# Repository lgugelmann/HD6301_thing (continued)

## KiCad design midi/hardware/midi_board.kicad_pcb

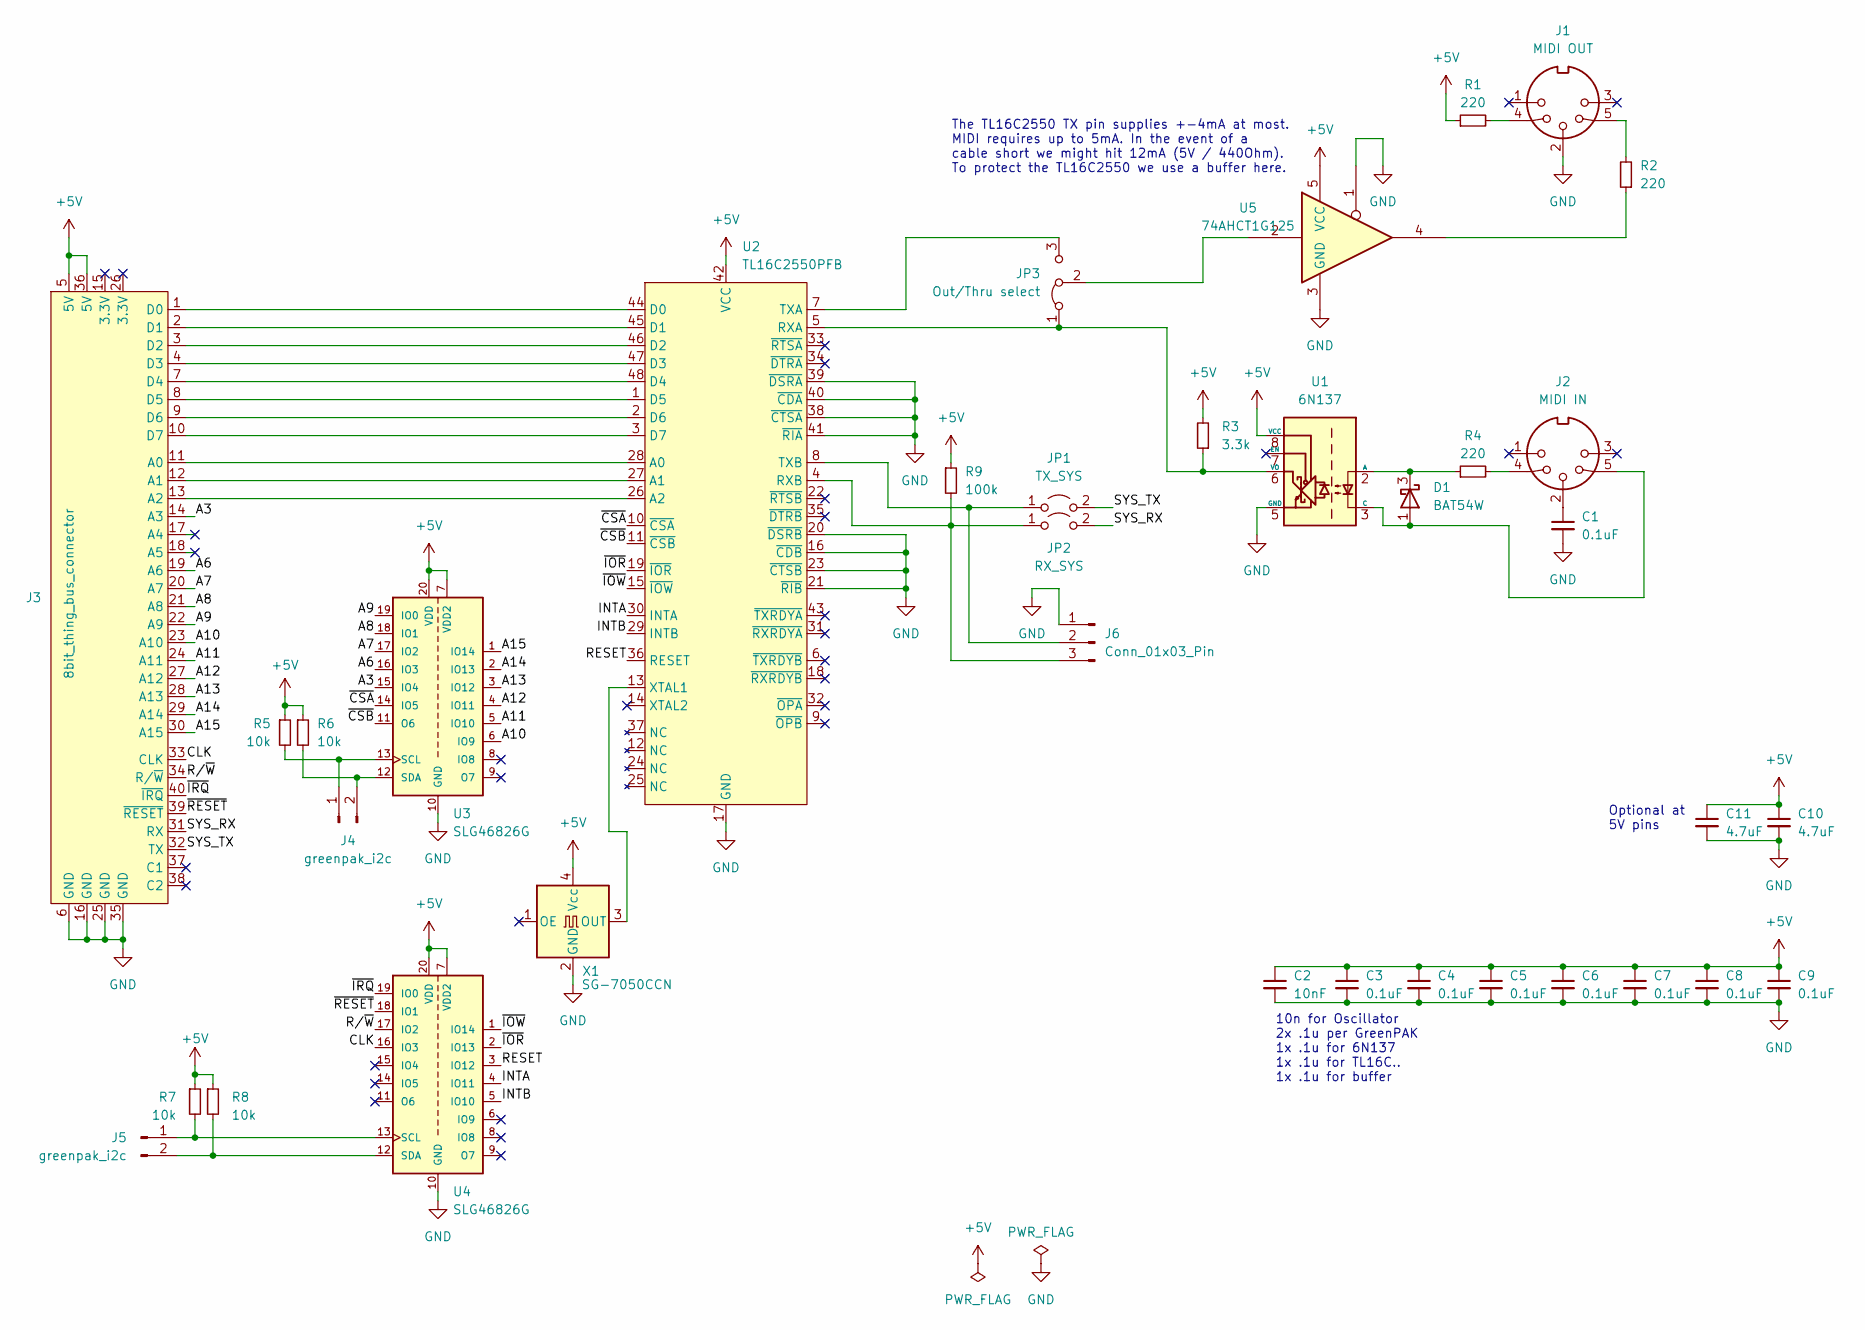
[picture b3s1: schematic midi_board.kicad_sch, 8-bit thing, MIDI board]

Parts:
C1, C3, C4, C5, C6, C7, C8, C9: 0.1uF; C_0805_2012Metric_Pad1.18x1.45mm_HandSolder
C2: 10nF; C_0805_2012Metric_Pad1.18x1.45mm_HandSolder
C10, C11: 4.7uF; C_0805_2012Metric_Pad1.18x1.45mm_HandSolder
D1: BAT54W; SOT-323_SC-70_Handsoldering
J1: MIDI OUT; Kycon-KCDX-5S-N
J2: MIDI IN; Kycon-KCDX-5S-N
J3: 8bit_thing_bus_connector; IDC-Header_2x20_P2.54mm_Horizontal
J4, J5: greenpak_i2c; PinHeader_1x02_P2.54mm_Vertical_minimal
J6: Conn_01x03_Pin; PinHeader_1x03_P2.54mm_Horizontal
JP1: TX_SYS; PinHeader_1x02_P2.54mm_Vertical_minimal
JP2: RX_SYS; PinHeader_1x02_P2.54mm_Vertical_minimal
JP3: Out/Thru select; PinHeader_1x03_P2.54mm_2_options_jumper_reverse
R1, R2: 220; R_0805_2012Metric_Pad1.20x1.40mm_HandSolder
R3: 3.3k; R_0805_2012Metric_Pad1.20x1.40mm_HandSolder
R4: 220; C_0805_2012Metric_Pad1.18x1.45mm_HandSolder
R5, R6, R7, R8: 10k; R_0805_2012Metric_Pad1.20x1.40mm_HandSolder
R9: 100k; R_0805_2012Metric_Pad1.20x1.40mm_HandSolder
U1: 6N137; DIP-8_W7.62mm
U2: TL16C2550PFB; TQFP-48_7x7mm_P0.5mm
U3, U4: SLG46826G; SOP65P640X120-20N; PARTREV 3.10
U5: 74AHCT1G125; SOT-353_SC-70-5_Handsoldering
X1: SG-7050CCN; Oscillator_SMD_SeikoEpson_SG8002CA-4Pin_7.0x5.0mm

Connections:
+5V: C2.1, C3.1, C4.1, C5.1, C6.1, C7.1, C8.1, C9.1, C10.1, C11.1, J3.5 (5V), J3.36 (5V), R1.1, R3.2, R5.1, R6.1, R7.1, R8.1, R9.1, U1.8 (VCC), U2.42 (VCC), U3.7 (VDD2), U3.20 (VDD), U4.7 (VDD2), U4.20 (VDD), U5.5 (VCC), X1.4 (Vcc)
/A3: J3.14 (A3), U3.15 (IO4)
/A6: J3.19 (A6), U3.16 (IO3)
/A7: J3.20 (A7), U3.17 (IO2)
/A8: J3.21 (A8), U3.18 (IO1)
/A9: J3.22 (A9), U3.19 (IO0)
/A10: J3.23 (A10), U3.6 (IO9)
/A11: J3.24 (A11), U3.5 (IO10)
/A12: J3.27 (A12), U3.4 (IO11)
/A13: J3.28 (A13), U3.3 (IO12)
/A14: J3.29 (A14), U3.2 (IO13)
/A15: J3.30 (A15), U3.1 (IO14)
/CLK: J3.33 (CLK), U4.16 (IO3)
/INTA: U2.30 (INTA), U4.4 (IO11)
/INTB: U2.29 (INTB), U4.5 (IO10)
/RESET: U2.36 (RESET), U4.3 (IO12)
/R/~W: J3.34 (R/~W), U4.17 (IO2)
/SYS_RX: J3.31 (RX), JP2.2 (B)
/SYS_TX: J3.32 (TX), JP1.2 (B)
/~CSA: U2.10 (~CSA), U3.14 (IO5)
/~CSB: U2.11 (~CSB), U3.11 (O6)
/~IOR: U2.19 (~IOR), U4.2 (IO13)
/~IOW: U2.15 (~IOW), U4.1 (IO14)
/~IRQ: J3.40 (~IRQ), U4.19 (IO0)
/~RESET: J3.39 (~RESET), U4.18 (IO1)
GND: C1.2, C2.2, C3.2, C4.2, C5.2, C6.2, C7.2, C8.2, C9.2, C10.2, C11.2, J1.2, J3.6 (GND), J3.16 (GND), J3.25 (GND), J3.35 (GND), J6.1, U1.5 (GND), U2.16 (~CDB), U2.17 (GND), U2.20 (~DSRB), U2.21 (~RIB), U2.23 (~CTSB), U2.38 (~CTSA), U2.39 (~DSRA), U2.40 (~CDA), U2.41 (~RIA), U3.10 (GND), U4.10 (GND), U5.1, U5.3 (GND), X1.2 (GND)
unnamed: C1.1, J2.2
unnamed: D1.1 (A), J2.5, U1.3 (C)
unnamed: D1.3 (K), R4.1, U1.2 (A)
unnamed: J1.4, R1.2
unnamed: J1.5, R2.2
unnamed: J2.4, R4.2
unnamed: J3.11 (A0), U2.28 (A0)
unnamed: J3.12 (A1), U2.27 (A1)
unnamed: J3.13 (A2), U2.26 (A2)
unnamed: J3.1 (D0), U2.44 (D0)
unnamed: J3.2 (D1), U2.45 (D1)
unnamed: J3.3 (D2), U2.46 (D2)
unnamed: J3.4 (D3), U2.47 (D3)
unnamed: J3.7 (D4), U2.48 (D4)
unnamed: J3.8 (D5), U2.1 (D5)
unnamed: J3.9 (D6), U2.2 (D6)
unnamed: J3.10 (D7), U2.3 (D7)
unnamed: J4.1, R5.2, U3.13 (SCL)
unnamed: J4.2, R6.2, U3.12 (SDA)
unnamed: J5.1, R7.2, U4.13 (SCL)
unnamed: J5.2, R8.2, U4.12 (SDA)
unnamed: J6.2, JP1.1 (A), U2.8 (TXB)
unnamed: J6.3, JP2.1 (A), R9.2, U2.4 (RXB)
unnamed: JP3.1 (A), R3.1, U1.6 (VO), U2.5 (RXA)
unnamed: JP3.3 (B), U2.7 (TXA)
unnamed: JP3.2 (C), U5.2
unnamed: R2.1, U5.4
unnamed: U2.13 (XTAL1), X1.3 (OUT)

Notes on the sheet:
The TL16C2550 TX pin supplies +-4mA at most. MIDI requires up to 5mA. In the event of a cable short we might hit 12mA (5V / 440Ohm). To protect the TL16C2550 we use a buffer here.
10n for Oscillator 2x .1u per GreenPAK 1x .1u for 6N137 1x .1u for TL16C.. 1x .1u for buffer
Optional at 5V pins

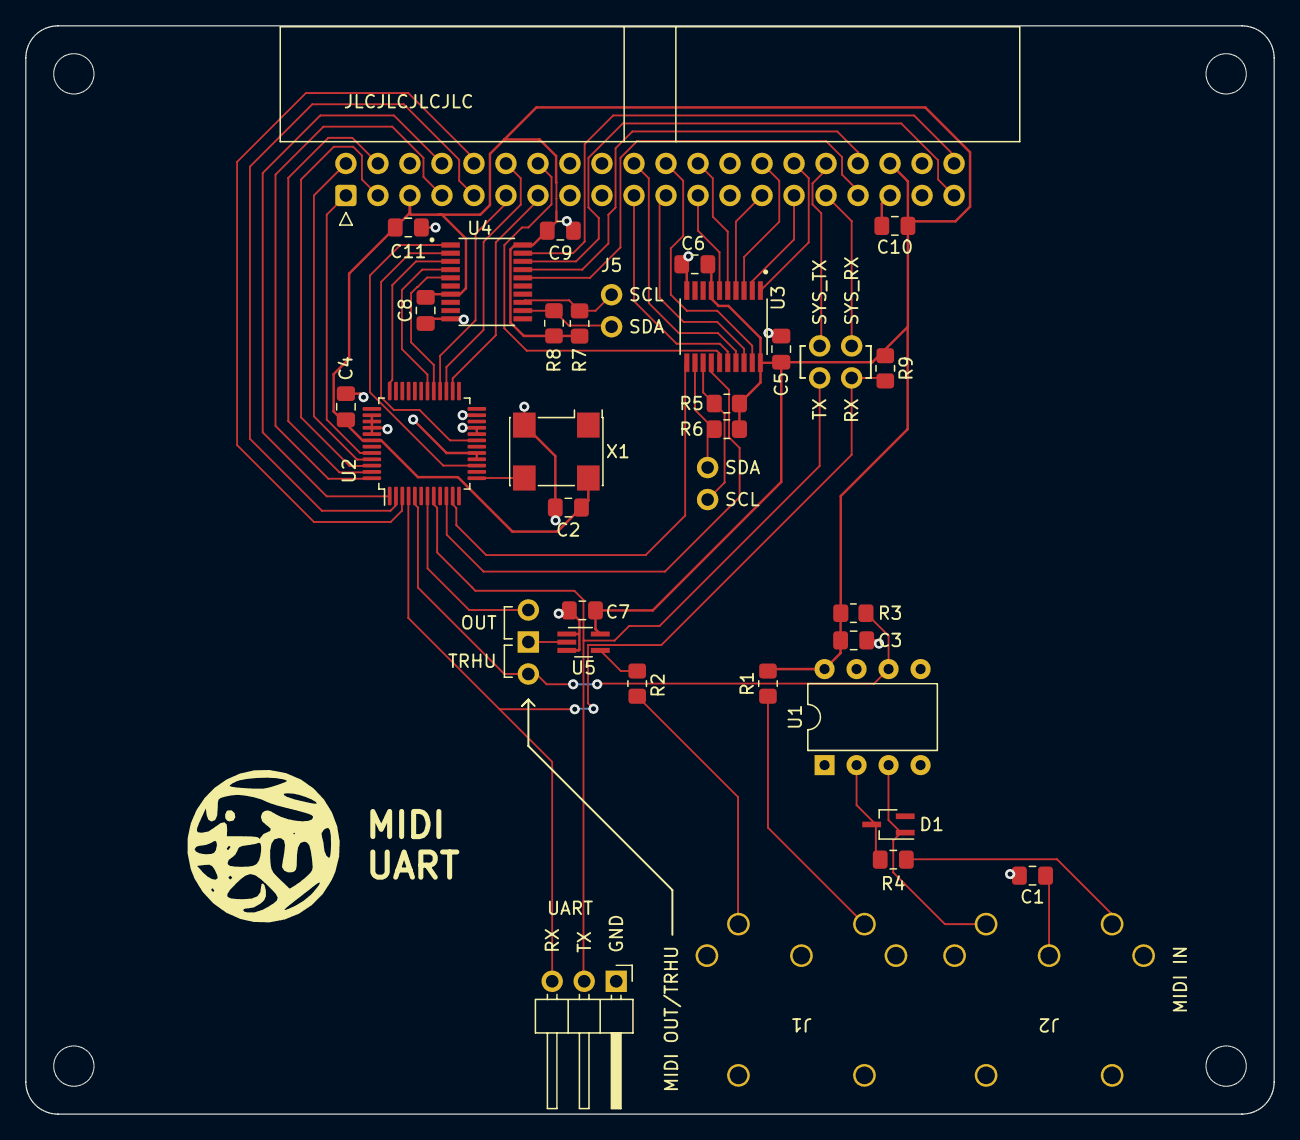
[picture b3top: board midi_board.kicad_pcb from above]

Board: 2 copper layers, 99.1 x 86.4 mm, 36 parts (0 on the bottom side), 54 nets.

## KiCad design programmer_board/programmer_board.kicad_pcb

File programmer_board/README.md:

# Pi Pico programmer board

> ***WARNING***
> the 1.0 version of the board is buggy. At a minimum it requires adding
> pullups on all OE pins. The Pico does not start quickly enough to put them into
> a good state. The resulting bus contention uses enough power to render the Pico
> unable to start. For any sane current limit the '5V' rail gets drawn down to
> less than the ~1.8V needed for the Pico boost converter to start working. The
> Schematic & PCB have not been updated to fix this bug yet. It's not hard to fix
> the v1.0 board by reworking some extra resistors onto it.

A common way to program ROMs for 8-bit hobby projects are ZIF sockets. Take ROM
out, put it into programmer, program it, put it back into the ZIF socket,
run. That works, but it gets tedious _really fast_. It's also getting harder and
harder to find parallel ROMs in DIP packages at reasonable prices. The solution
is to bite the bullet and use soldered-down ROMs in smaller packages and figure
out in-circuit programming.

The goal here is to make programming the HD6301 board as easy as programming an
Arduino from a modern computer, while at the same time keeping the HD6301 board
able to work independently without this development companion.

This is accomplished by having a Pi Pico expose a serial console to receive
commands from a computer. To program the HD6301 board the Pico puts the CPU into
standby mode, takes over the bus, reads or writes to arbitrary memory locations
(which allows it to program the ROM among other things), and wakes the HD6301
back up.

This technique makes for a fairly generic interface to many 8-bit era
devices. It could work easily for a 6502-based computer as well (at least for
versions with a bus-enable line).

Programming 8k (2 sectors) of ROM takes just a few seconds.

The board itself is pretty simple. The main issue is that the Pico does not have
enough I/O lines, and that it's not 5V tolerant. This means we need both
multiplexing and voltage translation. The address and data pins are all
connected in groups of 8 pins to a pair of 74LVC245 bus buffers and 74HCT573
latches. The latch holds the output data, while the '245 does voltage
translation for inputs. It's up to the software on the Pico to correctly juggle
the various output enable pins to avoid bus contention. The remaining lines are
voltage-translated by a GreenPAK programmable logic chip that can do 3.3V on
some GPIOs and 5V, tri-state on others.

The Pico was chosen here because it's trivial to prototype with it and it makes
it easy to expose 2 serial lines on the USB side. One is used for programming,
and one to communicate with the HD6301's own serial interface.

The initial plan was to use a much dumber chip like FTDI USB interfaces and put
all the logic on the other side of the serial interface. USB latency(!) made
that plan unworkable. See below for the details.

## TODOs for the next revision

- Add pull-ups on all OE pins and D0..D7 to guarantee safe initial state
- Jumpers for all power rails to isolate the Pico
- Some solution for power rail filtering. My desktop's USB ports are
  _NOISY_. Not a problem for digital work - but the OPL3 audio board suffers
  from bad filtering here.

## In-circuit programming via USB - the gory details

## FT231x solution

At first I explored using an FTDI FT231x. It's 5V compatible and conveniently
also gets us USB serial. It has an 8-pin bitbang mode and 4 additional 'CBUS'
lines. Those can be programmed to be GPIOs, write strobes, and more.

The first solution was to use the 8bit GPIOs for data and CBUS for control
lines. Unfortunately the CBUS GPIO mode can't be used concurrently with the
bitbang mode and switching between bitbang and CBUS takes a _long_ time (think
hundreds of ms). Switching between the two for every byte makes things
unworkably slow.

Next up I turned to putting glue logic on a GreenPAK chip and using the
write-strobe mode. This works really nicely: first write puts the chip in
standby, subsequent writes latch data, address low, address high onto '74xx573
latches, and after that the GreenPAK automatically strobes clock & R/W. After a
few hundred ms without activity everything resets and the 6301 wakes back up.

This works really nicely for a write-only in-circuit programmer. There is a
tested working python-based programmer and the necessary GreenPAK glue logic in
this repo. I didn't push for performance but got to ~15 seconds to write a 32K
ROM.

Next up I tried to figure out how to implement a read-mode as well. In theory it
should be easy: put a 74'245 on the data bus, do the same latching trick as
before, but instead at the end bring OE low on the '245 and read the FT231x I/O
pins. A CBUS line can be used to put the GreenPAK into a read-mode with
different strobes / timings, but because that needs to be done only once at the
start it should be fast enough.

I got this to work - but it's sloooow because of USB latency, se below for
why. Tl;dr: switching between reading / writing on the FT231x for every byte
takes >1ms each time. This means 1 minute to read the whole address space at a
minimum. The fastest I could manage is ~3ms per byte before I gave up.

There could be possible solutions that do not require switching between reading
and writing at each byte. One option is to use a CBUS line for a read strobe and
discrete logic to increment an address counter at each strobe. You could set up
the counter at the start, then put the chip into read mode, and stream the data
back. This starts to get a bit silly and would also require futzing around with
the FT231x read buffers which seem to be particularly tricky to synchronize to
anything.

Another option is to use a synchronous bit-bang mode where a read is done on
every write and streamed back. The catch here is that you have to decide ahead
of time which pins are inputs and which are outputs. I could split the 8 bits
into 4 in / 4 out but that would also require extra glue logic that I didn't
feel like building.

### USB latency ruins the party

USB communication (before 3.0) is _always_ host-initiated. No usb device can
just decide to send data. It needs to be asked by the host whether there is
anything that it might want to send first. The fastest polling rate available
from the host side is 1ms.

This means that if switching between reading and writing requires a control
packet there is a mandatory 1ms latency hit: 1 packet with the writes (which can
be all sent bunched up into one), then a second packet with the command to
switch from read to write, then another packet to poll for the read data. On the
ft231x that's 2ms latency / byte at a minimum as we need to wait out the polling
interval twice.

### Pi Pico programmer

To avoid USB latency I need something capable of receiving a "read x bytes
starting at address y" command and then stream the data back. I have a spare Pi
Pico laying around so I went with that. It has enough I/O, has support for
multiple UARTs (so one for programming, one for comms with the HD6301), and
comes with both 5V and 3.3V rail which can be convenient. Downside: not 5V
tolerant.

The 5V issue is easy to solve: for the data output from the Pico I use
TTL-compatible '74xxT573 latches, for the data input to the Pico 3.3V '74LVHC245
buffers which are 5V tolerant. For the control lines I make use of the dual
supply feature of the _really really cool_ SLG46826 GreenPAK to have 3.3V I/O on
the Pico side and tri-state 5V I/O on the HD6301 bus side.

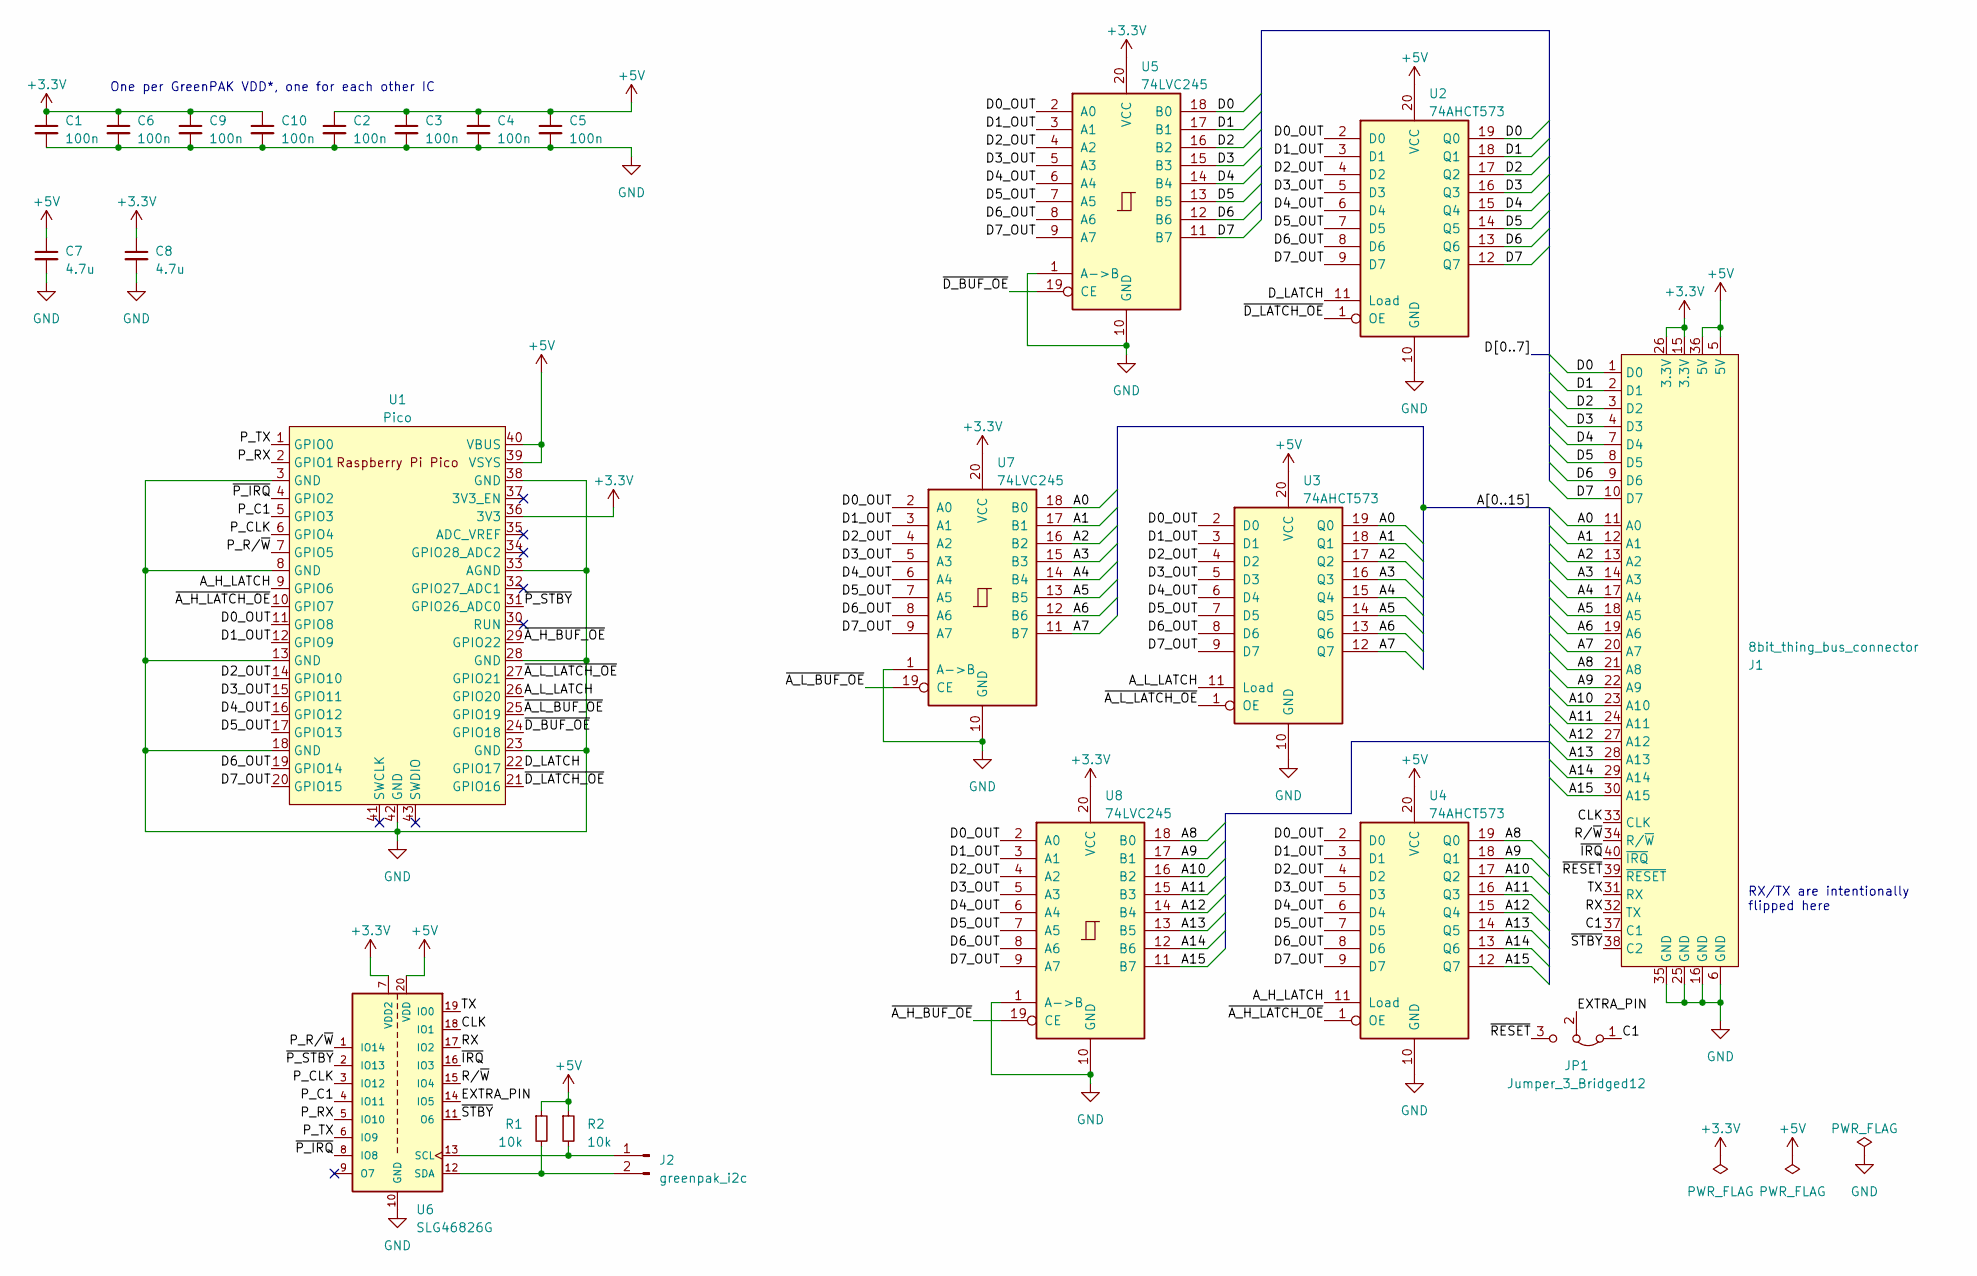
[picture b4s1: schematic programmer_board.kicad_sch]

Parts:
C1, C2, C3, C4, C5, C6, C9, C10: 100n; C_0805_2012Metric_Pad1.18x1.45mm_HandSolder
C7, C8: 4.7u; C_0805_2012Metric_Pad1.18x1.45mm_HandSolder
J1: 8bit_thing_bus_connector; IDC-Header_2x20_P2.54mm_Horizontal
J2: greenpak_i2c; PinHeader_1x02_P2.54mm_Vertical_minimal
JP1: Jumper_3_Bridged12; PinHeader_1x03_P2.54mm_Vertical
R1, R2: 10k; R_0805_2012Metric_Pad1.20x1.40mm_HandSolder
U1: Pico; RPi_Pico_SMD_TH
U2, U3, U4: 74AHCT573; SSOP-20_5.3x7.2mm_P0.65mm
U5, U7, U8: 74LVC245; TSSOP-20_4.4x6.5mm_P0.65mm
U6: SLG46826G; SOP65P640X120-20N; PARTREV 3.10

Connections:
+3.3V: C1.1, C6.1, C8.1, C9.1, C10.1, J1.15 (3.3V), J1.26 (3.3V), U1.36 (3V3), U5.20 (VCC), U6.7 (VDD2), U7.20 (VCC), U8.20 (VCC)
+5V: C2.1, C3.1, C4.1, C5.1, C7.1, J1.5 (5V), J1.36 (5V), R1.1, R2.1, U1.39 (VSYS), U1.40 (VBUS), U2.20 (VCC), U3.20 (VCC), U4.20 (VCC), U6.20 (VDD)
/A0: J1.11 (A0), U3.19 (Q0), U7.18 (B0)
/A1: J1.12 (A1), U3.18 (Q1), U7.17 (B1)
/A2: J1.13 (A2), U3.17 (Q2), U7.16 (B2)
/A3: J1.14 (A3), U3.16 (Q3), U7.15 (B3)
/A4: J1.17 (A4), U3.15 (Q4), U7.14 (B4)
/A5: J1.18 (A5), U3.14 (Q5), U7.13 (B5)
/A6: J1.19 (A6), U3.13 (Q6), U7.12 (B6)
/A7: J1.20 (A7), U3.12 (Q7), U7.11 (B7)
/A8: J1.21 (A8), U4.19 (Q0), U8.18 (B0)
/A9: J1.22 (A9), U4.18 (Q1), U8.17 (B1)
/A10: J1.23 (A10), U4.17 (Q2), U8.16 (B2)
/A11: J1.24 (A11), U4.16 (Q3), U8.15 (B3)
/A12: J1.27 (A12), U4.15 (Q4), U8.14 (B4)
/A13: J1.28 (A13), U4.14 (Q5), U8.13 (B5)
/A14: J1.29 (A14), U4.13 (Q6), U8.12 (B6)
/A15: J1.30 (A15), U4.12 (Q7), U8.11 (B7)
/A_H_LATCH: U1.9 (GPIO6), U4.11 (Load)
/A_L_LATCH: U1.26 (GPIO20), U3.11 (Load)
/C1: J1.37 (C1), JP1.1 (A)
/CLK: J1.33 (CLK), U6.18 (IO1)
/D0: J1.1 (D0), U2.19 (Q0), U5.18 (B0)
/D0_OUT: U1.11 (GPIO8), U2.2 (D0), U3.2 (D0), U4.2 (D0), U5.2 (A0), U7.2 (A0), U8.2 (A0)
/D1: J1.2 (D1), U2.18 (Q1), U5.17 (B1)
/D1_OUT: U1.12 (GPIO9), U2.3 (D1), U3.3 (D1), U4.3 (D1), U5.3 (A1), U7.3 (A1), U8.3 (A1)
/D2: J1.3 (D2), U2.17 (Q2), U5.16 (B2)
/D2_OUT: U1.14 (GPIO10), U2.4 (D2), U3.4 (D2), U4.4 (D2), U5.4 (A2), U7.4 (A2), U8.4 (A2)
/D3: J1.4 (D3), U2.16 (Q3), U5.15 (B3)
/D3_OUT: U1.15 (GPIO11), U2.5 (D3), U3.5 (D3), U4.5 (D3), U5.5 (A3), U7.5 (A3), U8.5 (A3)
/D4: J1.7 (D4), U2.15 (Q4), U5.14 (B4)
/D4_OUT: U1.16 (GPIO12), U2.6 (D4), U3.6 (D4), U4.6 (D4), U5.6 (A4), U7.6 (A4), U8.6 (A4)
/D5: J1.8 (D5), U2.14 (Q5), U5.13 (B5)
/D5_OUT: U1.17 (GPIO13), U2.7 (D5), U3.7 (D5), U4.7 (D5), U5.7 (A5), U7.7 (A5), U8.7 (A5)
/D6: J1.9 (D6), U2.13 (Q6), U5.12 (B6)
/D6_OUT: U1.19 (GPIO14), U2.8 (D6), U3.8 (D6), U4.8 (D6), U5.8 (A6), U7.8 (A6), U8.8 (A6)
/D7: J1.10 (D7), U2.12 (Q7), U5.11 (B7)
/D7_OUT: U1.20 (GPIO15), U2.9 (D7), U3.9 (D7), U4.9 (D7), U5.9 (A7), U7.9 (A7), U8.9 (A7)
/D_LATCH: U1.22 (GPIO17), U2.11 (Load)
/EXTRA_PIN: JP1.2 (C), U6.14 (IO5)
/P_C1: U1.5 (GPIO3), U6.4 (IO11)
/P_CLK: U1.6 (GPIO4), U6.3 (IO12)
/P_RX: U1.2 (GPIO1), U6.5 (IO10)
/P_R/~W: U1.7 (GPIO5), U6.1 (IO14)
/P_TX: U1.1 (GPIO0), U6.6 (IO9)
/RX: J1.32 (TX), U6.17 (IO2)
/R/~W: J1.34 (R/~W), U6.15 (IO4)
/TX: J1.31 (RX), U6.19 (IO0)
/~A_H_BUF_OE: U1.29 (GPIO22), U8.19 (CE)
/~A_H_LATCH_OE: U1.10 (GPIO7), U4.1 (OE)
/~A_L_BUF_OE: U1.25 (GPIO19), U7.19 (CE)
/~A_L_LATCH_OE: U1.27 (GPIO21), U3.1 (OE)
/~D_BUF_OE: U1.24 (GPIO18), U5.19 (CE)
/~D_LATCH_OE: U1.21 (GPIO16), U2.1 (OE)
/~IRQ: J1.40 (~IRQ), U6.16 (IO3)
/~P_IRQ: U1.4 (GPIO2), U6.8 (IO8)
/~P_STBY: U1.31 (GPIO26_ADC0), U6.2 (IO13)
/~RESET: J1.39 (~RESET), JP1.3 (B)
/~STBY: J1.38 (C2), U6.11 (O6)
GND: C1.2, C2.2, C3.2, C4.2, C5.2, C6.2, C7.2, C8.2, C9.2, C10.2, J1.6 (GND), J1.16 (GND), J1.25 (GND), J1.35 (GND), U1.3 (GND), U1.8 (GND), U1.13 (GND), U1.18 (GND), U1.23 (GND), U1.28 (GND), U1.33 (AGND), U1.38 (GND), U1.42 (GND), U2.10 (GND), U3.10 (GND), U4.10 (GND), U5.1 (A->B), U5.10 (GND), U6.10 (GND), U7.1 (A->B), U7.10 (GND), U8.1 (A->B), U8.10 (GND)
unnamed: J2.1, R2.2, U6.13 (SCL)
unnamed: J2.2, R1.2, U6.12 (SDA)

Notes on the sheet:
RX/TX are intentionally flipped here
One per GreenPAK VDD*, one for each other IC

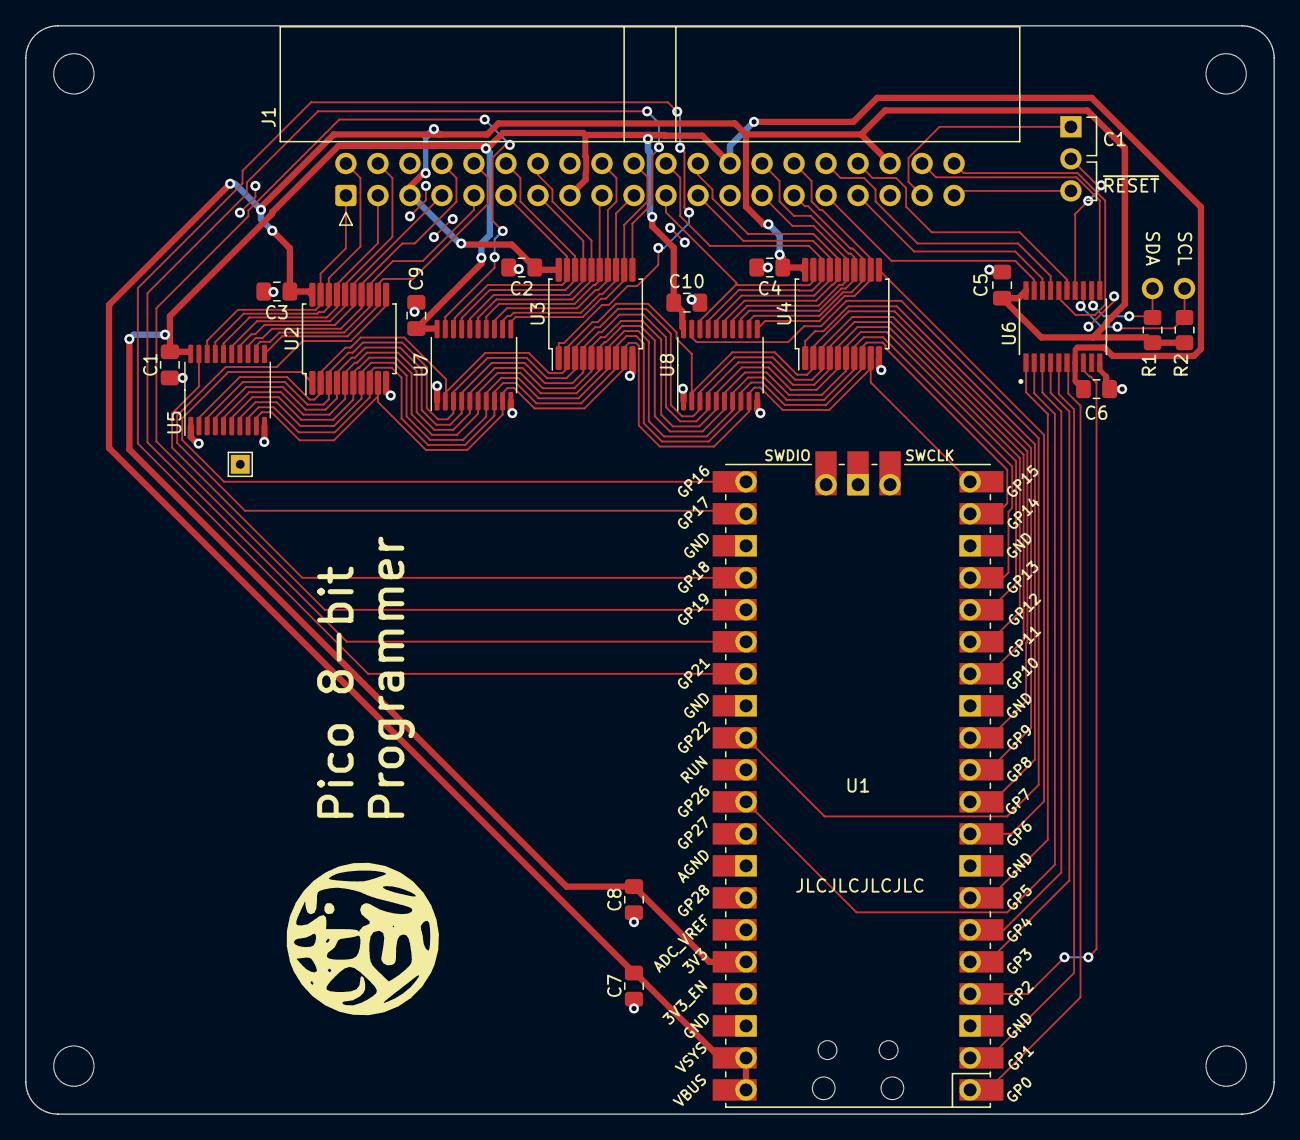
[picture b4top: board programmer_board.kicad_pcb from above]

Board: 2 copper layers, 99.1 x 86.4 mm, 23 parts (0 on the bottom side), 62 nets.

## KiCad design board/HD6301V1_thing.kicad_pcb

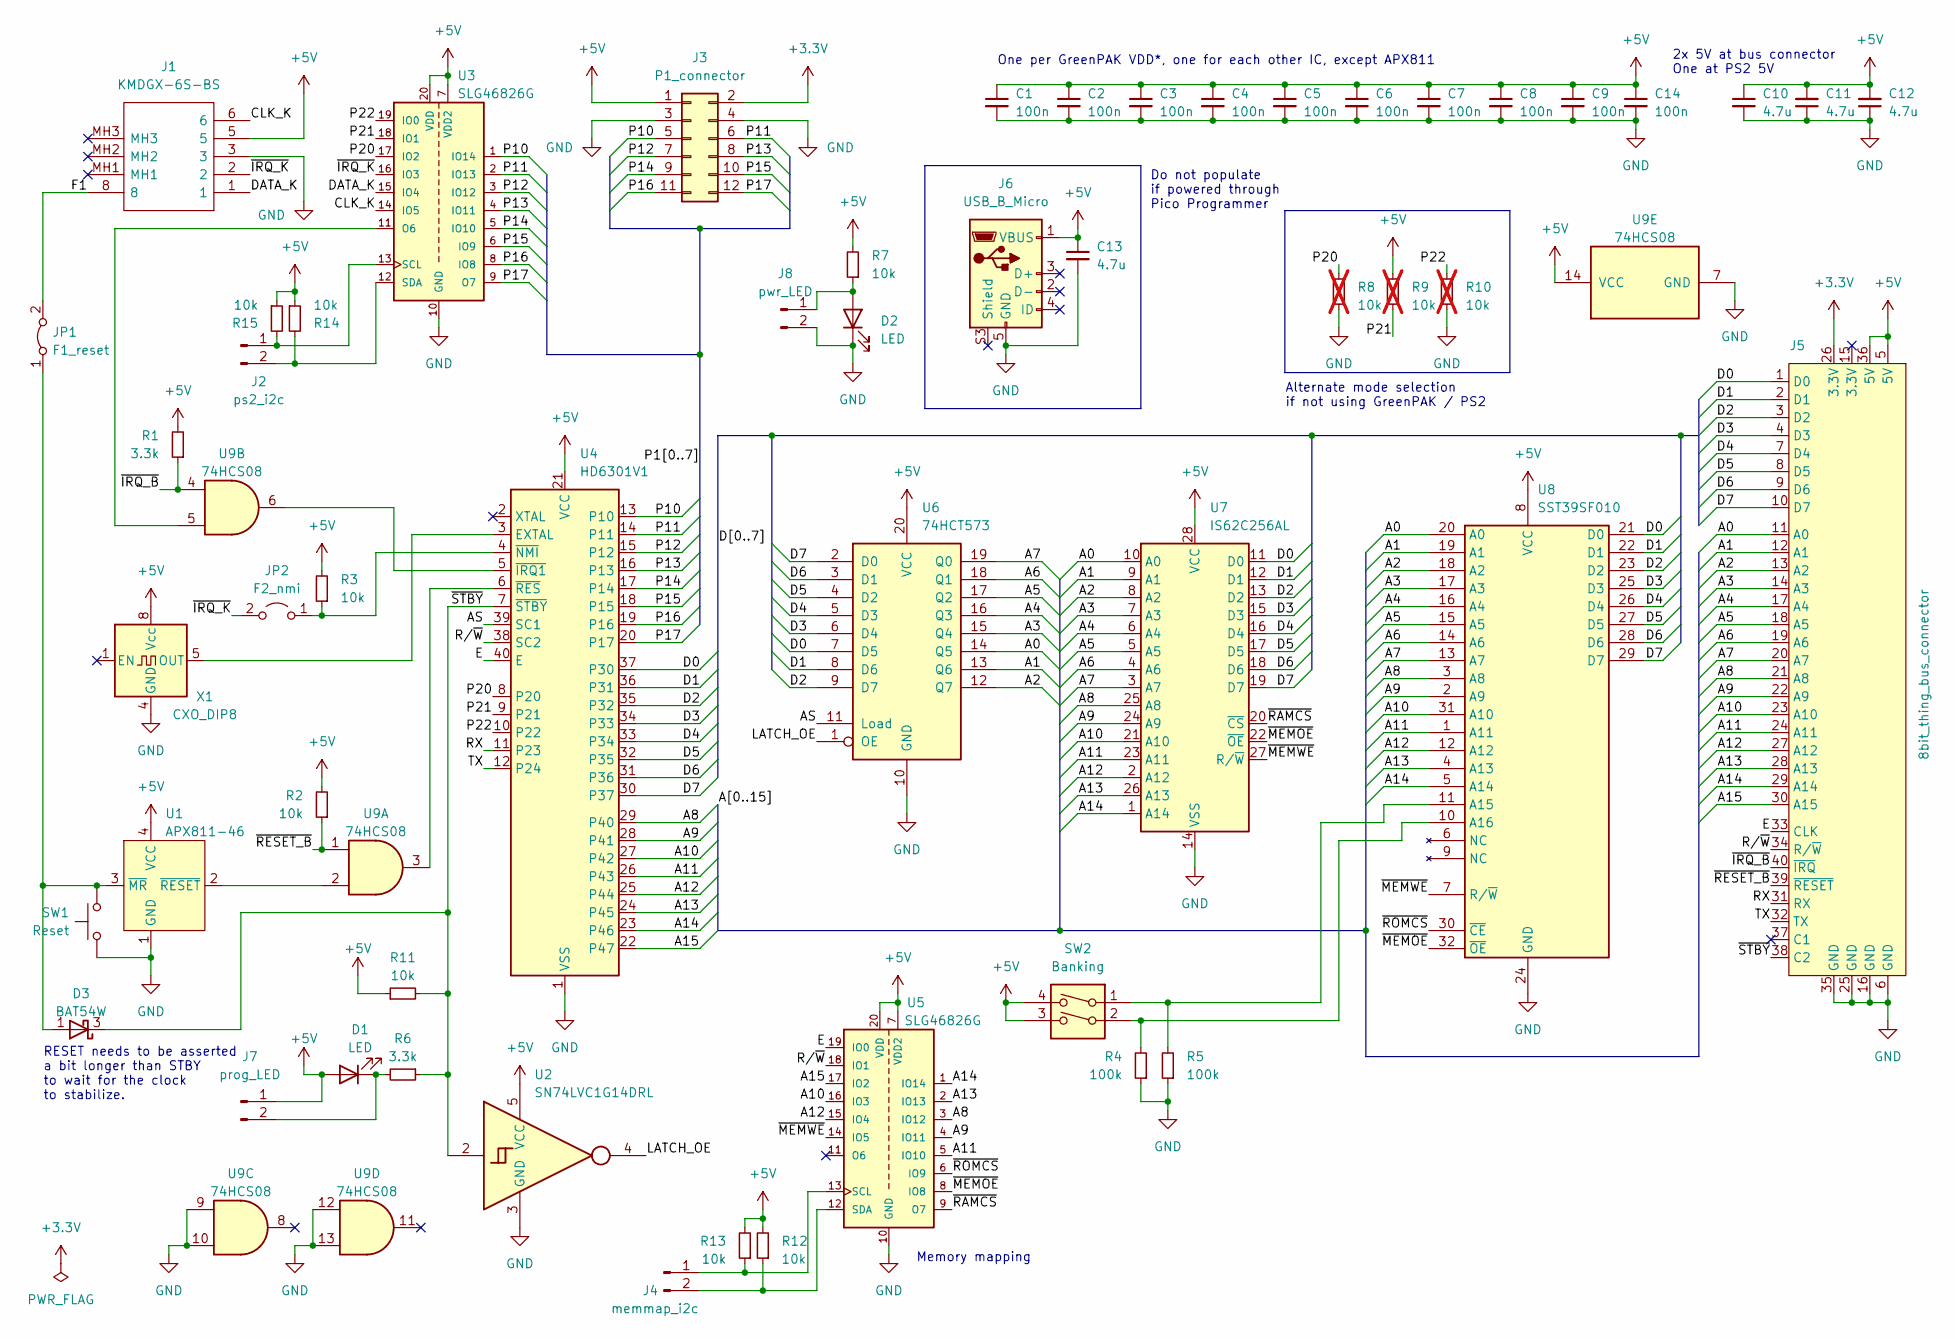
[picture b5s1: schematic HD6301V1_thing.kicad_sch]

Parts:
C1, C2, C3, C4, C5, C6, C7, C8, C9, C14: 100n; C_0805_2012Metric_Pad1.18x1.45mm_HandSolder
C10, C11, C12, C13: 4.7u; C_0805_2012Metric_Pad1.18x1.45mm_HandSolder
D1, D2: LED; LED_0805_2012Metric_Pad1.15x1.40mm_HandSolder
D3: BAT54W; SOT-323_SC-70_Handsoldering
J1: KMDGX-6S-BS; KMDGX6SBS; Manufacturer_Part_Number KMDGX-6S-BS; Mouser Part Number 806-KMDGX-6S-BS
J2: ps2_i2c; PinHeader_1x02_P2.54mm_Vertical_minimal
J3: P1_connector; PinHeader_2x06_P2.54mm_Horizontal_no_graphics
J4: memmap_i2c; PinHeader_1x02_P2.54mm_Vertical_minimal
J5: 8bit_thing_bus_connector; IDC-Header_2x20_P2.54mm_Horizontal
J6: USB_B_Micro; AMPHENOL_10118194-0001LF_MICRO_USB_improved
J7: prog_LED; PinHeader_1x02_P2.54mm_Vertical_minimal
J8: pwr_LED; PinHeader_1x02_P2.54mm_Vertical_minimal
JP1: F1_reset; PinHeader_1x02_P2.54mm_Vertical_minimal
JP2: F2_nmi; PinHeader_1x02_P2.54mm_Vertical_minimal
R1, R6: 3.3k; R_0805_2012Metric_Pad1.20x1.40mm_HandSolder
R2, R3, R7, R11, R12, R13, R14, R15: 10k; R_0805_2012Metric_Pad1.20x1.40mm_HandSolder
R4, R5: 100k; R_0805_2012Metric_Pad1.20x1.40mm_HandSolder
R8, R9, R10: 10k; R_0805_2012Metric_Pad1.20x1.40mm_HandSolder; not fitted
SW1: Reset; SW_SPST_TL3305A
SW2: Banking; SW_DS04-254-1L-02BK
U1: APX811-46; SOT-143_Handsoldering
U2: SN74LVC1G14DRL; SOT-353_SC-70-5_Handsoldering
U3, U5: SLG46826G; SOP65P640X120-20N; PARTREV 3.10
U4: HD6301V1; DIP-40_W15.24mm_Socket
U6: 74HCT573; SOIC-20W_7.5x12.8mm_P1.27mm
U7: IS62C256AL; SOIC127P1210X305-28N
U8: SST39SF010; TSOP-I-32_12.4x8mm_P0.5mm
U9: 74HCS08; TSSOP-14_4.4x5mm_P0.65mm
X1: CXO_DIP8; Oscillator_DIP-8

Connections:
+3.3V: J3.2, J5.26 (3.3V)
+5V: C1.1, C2.1, C3.1, C4.1, C5.1, C6.1, C7.1, C8.1, C9.1, C10.1, C11.2, C12.2, C13.1, C14.1, D1.2 (A), J1.5, J3.1, J5.5 (5V), J5.36 (5V), J6.1 (VBUS), J7.1, R1.2, R2.2, R3.2, R7.2, R9.2, R11.1, R12.2, R13.2, R14.1, R15.1, SW2.3, SW2.4, U1.4 (VCC), U2.5 (VCC), U3.7 (VDD2), U3.20 (VDD), U4.21 (VCC), U5.7 (VDD2), U5.20 (VDD), U6.20 (VCC), U7.28 (VCC), U8.8 (VCC), U9.14 (VCC), X1.8 (Vcc)
/A0: J5.11 (A0), U6.14 (Q5), U7.10 (A0), U8.20 (A0)
/A1: J5.12 (A1), U6.13 (Q6), U7.9 (A1), U8.19 (A1)
/A2: J5.13 (A2), U6.12 (Q7), U7.8 (A2), U8.18 (A2)
/A3: J5.14 (A3), U6.15 (Q4), U7.7 (A3), U8.17 (A3)
/A4: J5.17 (A4), U6.16 (Q3), U7.6 (A4), U8.16 (A4)
/A5: J5.18 (A5), U6.17 (Q2), U7.5 (A5), U8.15 (A5)
/A6: J5.19 (A6), U6.18 (Q1), U7.4 (A6), U8.14 (A6)
/A7: J5.20 (A7), U6.19 (Q0), U7.3 (A7), U8.13 (A7)
/A8: J5.21 (A8), U4.29 (P40), U5.3 (IO12), U7.25 (A8), U8.3 (A8)
/A9: J5.22 (A9), U4.28 (P41), U5.4 (IO11), U7.24 (A9), U8.2 (A9)
/A10: J5.23 (A10), U4.27 (P42), U5.16 (IO3), U7.21 (A10), U8.31 (A10)
/A11: J5.24 (A11), U4.26 (P43), U5.5 (IO10), U7.23 (A11), U8.1 (A11)
/A12: J5.27 (A12), U4.25 (P44), U5.15 (IO4), U7.2 (A12), U8.12 (A12)
/A13: J5.28 (A13), U4.24 (P45), U5.2 (IO13), U7.26 (A13), U8.4 (A13)
/A14: J5.29 (A14), U4.23 (P46), U5.1 (IO14), U7.1 (A14), U8.5 (A14)
/A15: J5.30 (A15), U4.22 (P47), U5.17 (IO2)
/AS: U4.39 (SC1), U6.11 (Load)
/CLK_K: J1.6, U3.14 (IO5)
/D0: J5.1 (D0), U4.37 (P30), U6.7 (D5), U7.11 (D0), U8.21 (D0)
/D1: J5.2 (D1), U4.36 (P31), U6.8 (D6), U7.12 (D1), U8.22 (D1)
/D2: J5.3 (D2), U4.35 (P32), U6.9 (D7), U7.13 (D2), U8.23 (D2)
/D3: J5.4 (D3), U4.34 (P33), U6.6 (D4), U7.15 (D3), U8.25 (D3)
/D4: J5.7 (D4), U4.33 (P34), U6.5 (D3), U7.16 (D4), U8.26 (D4)
/D5: J5.8 (D5), U4.32 (P35), U6.4 (D2), U7.17 (D5), U8.27 (D5)
/D6: J5.9 (D6), U4.31 (P36), U6.3 (D1), U7.18 (D6), U8.28 (D6)
/D7: J5.10 (D7), U4.30 (P37), U6.2 (D0), U7.19 (D7), U8.29 (D7)
/DATA_K: J1.1, U3.15 (IO4)
/E: J5.33 (CLK), U4.40 (E), U5.19 (IO0)
/F1: J1.8, JP1.2 (B)
/LATCH_OE: U2.4, U6.1 (OE)
/P10: J3.5, U3.1 (IO14), U4.13 (P10)
/P11: J3.6, U3.2 (IO13), U4.14 (P11)
/P12: J3.7, U3.3 (IO12), U4.15 (P12)
/P13: J3.8, U3.4 (IO11), U4.16 (P13)
/P14: J3.9, U3.5 (IO10), U4.17 (P14)
/P15: J3.10, U3.6 (IO9), U4.18 (P15)
/P16: J3.11, U3.8 (IO8), U4.19 (P16)
/P17: J3.12, U3.9 (O7), U4.20 (P17)
/P20: R8.2, U3.17 (IO2), U4.8 (P20)
/P21: R9.1, U3.18 (IO1), U4.9 (P21)
/P22: R10.2, U3.19 (IO0), U4.10 (P22)
/RX: J5.31 (RX), U4.11 (P23)
/R/~W: J5.34 (R/~W), U4.38 (SC2), U5.18 (IO1)
/TX: J5.32 (TX), U4.12 (P24)
/~IRQ_B: J5.40 (~IRQ), R1.1, U9.4
/~IRQ_K: J1.2, JP2.2 (B), U3.16 (IO3)
/~MEMOE: U5.8 (IO8), U7.22 (~OE), U8.32 (~OE)
/~MEMWE: U5.14 (IO5), U7.27 (R/~W), U8.7 (R/~W)
/~RAMCS: U5.9 (O7), U7.20 (~CS)
/~RESET_B: J5.39 (~RESET), R2.1, U9.1
/~ROMCS: U5.6 (IO9), U8.30 (~CE)
/~STBY: D3.3 (K), J5.38 (C2), R6.1, R11.2, U2.2, U4.7 (~STBY)
GND: C1.2, C2.2, C3.2, C4.2, C5.2, C6.2, C7.2, C8.2, C9.2, C10.2, C11.1, C12.1, C13.2, C14.2, D2.1 (K), J1.3, J3.3, J3.4, J5.6 (GND), J5.16 (GND), J5.25 (GND), J5.35 (GND), J6.5 (GND), J8.2, R4.1, R5.1, R8.1, R10.1, SW1.1, U1.1 (GND), U2.3 (GND), U3.10 (GND), U4.1 (VSS), U5.10 (GND), U6.10 (GND), U7.14 (VSS), U8.24 (GND), U9.7 (GND), U9.9, U9.10, U9.12, U9.13, X1.4 (GND)
unnamed: D1.1 (K), J7.2, R6.2
unnamed: D2.2 (A), J8.1, R7.1
unnamed: D3.1 (A), JP1.1 (A), SW1.2, U1.3 (~MR)
unnamed: J2.1, R15.2, U3.13 (SCL)
unnamed: J2.2, R14.2, U3.12 (SDA)
unnamed: J4.1, R13.1, U5.13 (SCL)
unnamed: J4.2, R12.1, U5.12 (SDA)
unnamed: JP2.1 (A), R3.1, U4.4 (~NMI)
unnamed: U1.2 (~RESET), U9.2
unnamed: U3.11 (O6), U9.5
unnamed: U4.3 (EXTAL), X1.5 (OUT)
unnamed: U4.5 (~IRQ1), U9.6
unnamed: U4.6 (~RES), U9.3
unnamed: R5.2, SW2.1, U8.11 (A15)
unnamed: R4.2, SW2.2, U8.10 (A16)

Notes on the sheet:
RESET needs to be asserted a bit longer than STBY to wait for the clock to stabilize.
Memory mapping
Alternate mode selection if not using GreenPAK / PS2
Do not populate if powered through Pico Programmer
2x 5V at bus connector One at PS2 5V
One per GreenPAK VDD*, one for each other IC, except APX811

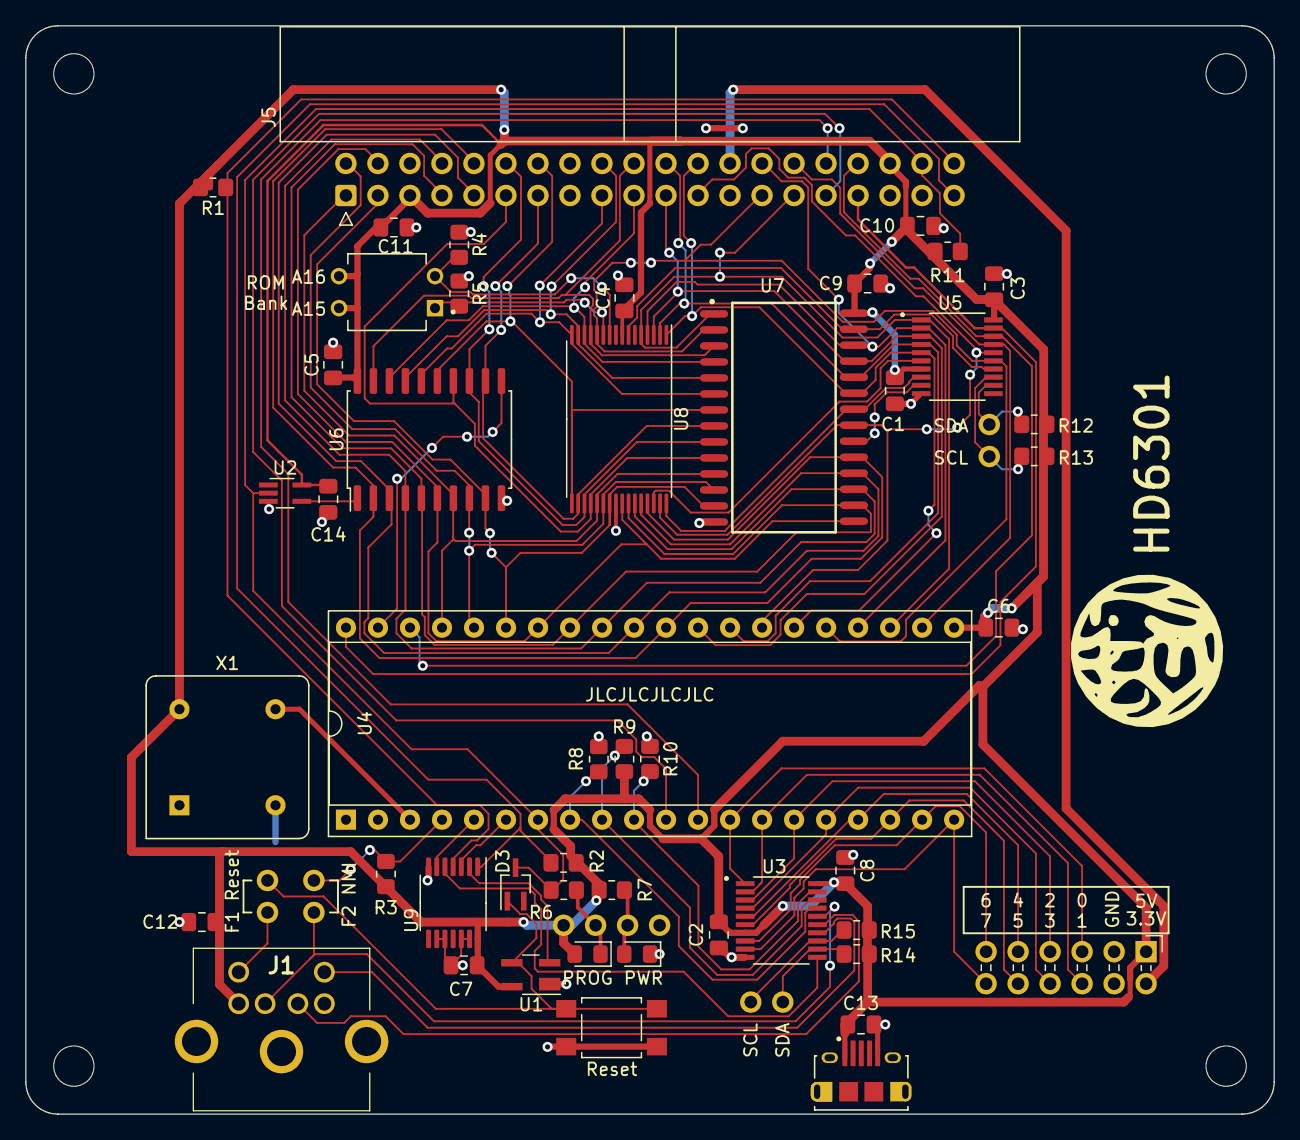
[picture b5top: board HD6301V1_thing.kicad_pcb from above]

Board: 2 copper layers, 99.1 x 86.4 mm, 54 parts (0 on the bottom side), 70 nets.
